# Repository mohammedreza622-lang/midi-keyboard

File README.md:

# midi-keyboard

ive finally completed the midi keypad it was truly an amazing exerience 
, as you can see i opted for this futuristic weird polygonal design to give it some character along with 3 switces 3 leds an esp32 s3-e an ec11 and finally my trick in the book the io extender

heres the schematic 

the footprints

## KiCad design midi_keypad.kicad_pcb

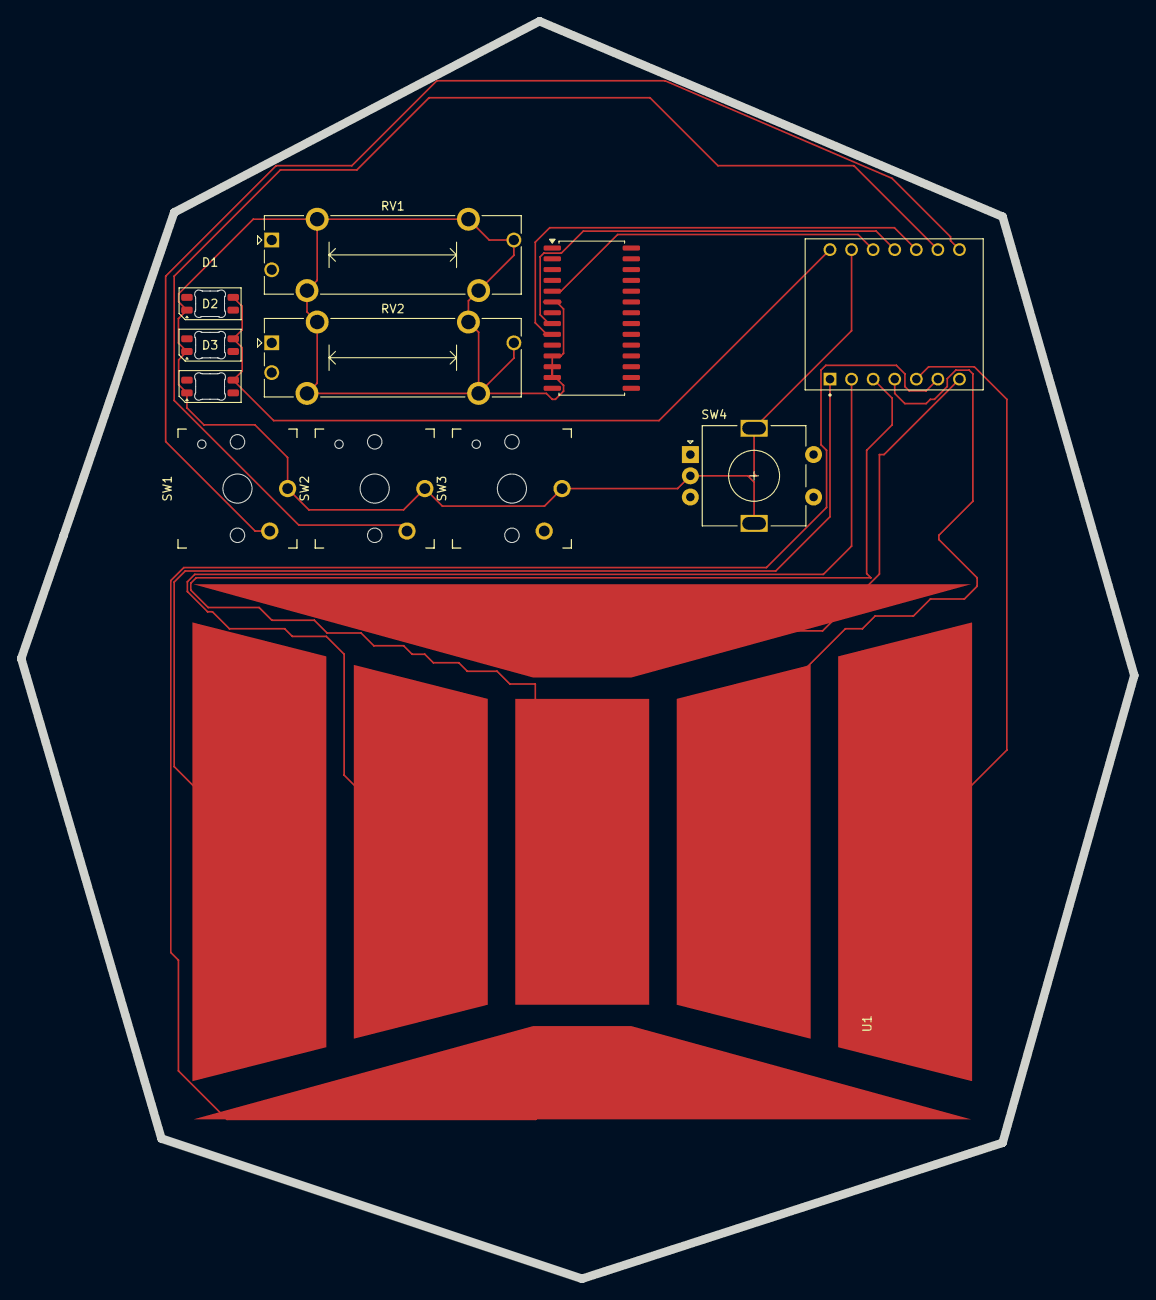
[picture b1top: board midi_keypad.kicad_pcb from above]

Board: 2 copper layers, 131.0 x 148.0 mm, 12 parts (0 on the bottom side), 22 nets.

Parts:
D1, D2, D3: SK6812MINI-E; LED_SK6812MINI-E_3.2x2.8mm_P1.5mm_ReverseMount
J2: Conn_01x07; pads
RV1, RV2: R_Potentiometer_MountingPin; Potentiometer_Bourns_PTA1543_Single_Slide
SW1, SW2, SW3: SW_Push; Kailh Choc Low-Profile Switches
SW4: RotaryEncoder_Switch_MP; RotaryEncoder_Alps_EC11E-Switch_Vertical_H20mm
U1: XIAO-ESP32-S3; XIAO ESP32-S3
U2: MCP23017x-x-ML; SOIC-28W_7.5x17.9mm_P1.27mm

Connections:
+3.3V: RV1.1, RV2.1, U1.12 (3V3), U2.5 (V_{DD})
+5V: D1.3 (VDD), D2.3 (VDD), D3.3 (VDD), U1.14 (5V)
/ENC1_A: SW4.A, U2.18 (GPA1)
/ENC1_B: SW4.B, U2.19 (GPA2)
/LED: D1.2 (DIN), U2.22 (GPA5)
/SLIDE1: RV1.2, U2.20 (GPA3)
/SLIDE2: RV2.2, U2.21 (GPA4)
/SWITCH1: SW1.2, U1.8 (D7/GPIO44)
/SWITCH2: SW2.2, U1.9 (D8/GPIO7)
/SWITCH3: SW3.2, U2.17 (GPA0)
/TOUCH1: J2.1, U1.1 (D0/GPIO1)
/TOUCH2: J2.2, U1.2 (D1/GPIO2)
/TOUCH3: J2.3, U1.3 (D2/GPIO3)
/TOUCH4: J2.4, U1.4 (D3/GPIO4)
/TOUCH5: J2.5, U1.5 (D4/GPIO5)
/TOUCH6: J2.6, U1.6 (D5/GPIO6)
/TOUCH7: J2.7, U1.7 (D6/GPIO43)
GND: D1.1 (VSS), D2.1 (VSS), D3.1 (VSS), RV1.3, RV1.MP (MountPin), RV2.3, RV2.MP (MountPin), SW1.1, SW2.1, SW3.1, SW4.C, SW4.MP, U1.13 (GND), U2.6 (V_{SS}), U2.11 (A0), U2.12 (A1), U2.13 (A2)
unnamed: D1.4 (DOUT), D2.2 (DIN)
unnamed: D2.4 (DOUT), D3.2 (DIN)
unnamed: U1.10 (D9/GPIO8), U2.9 (SDA)
unnamed: U1.11 (D10/GPIO9), U2.8 (SCK)

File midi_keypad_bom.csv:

Designator,Footprint,Quantity,Value,LCSC Part #
"D1, D2, D3",LED_SK6812MINI-E_3.2x2.8mm_P1.5mm_ReverseMount,3,SK6812MINI-E,
J2,pads,1,Conn_01x07,
"RV1, RV2",Potentiometer_Bourns_PTA1543_Single_Slide,2,R_Potentiometer_MountingPin,
"SW1, SW2, SW3",Kailh Choc Low-Profile Switches,3,SW_Push,
SW4,RotaryEncoder_Alps_EC11E-Switch_Vertical_H20mm,1,RotaryEncoder_Switch_MP,
U1,XIAO ESP32-S3,1,XIAO-ESP32-S3,
U2,SOIC-28W_7.5x17.9mm_P1.27mm,1,MCP23017x-x-ML,
